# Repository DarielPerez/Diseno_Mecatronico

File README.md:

Este repositorio contiene material relacionado al diseño mecatronico desde documentos hasta diseños de pcb y mucho más abarcando eletronica, diseño 3D, busqueda de informacion, diesño de PCB, diagramas de circuitos, programacion entre otros.

By: Dariel Perez

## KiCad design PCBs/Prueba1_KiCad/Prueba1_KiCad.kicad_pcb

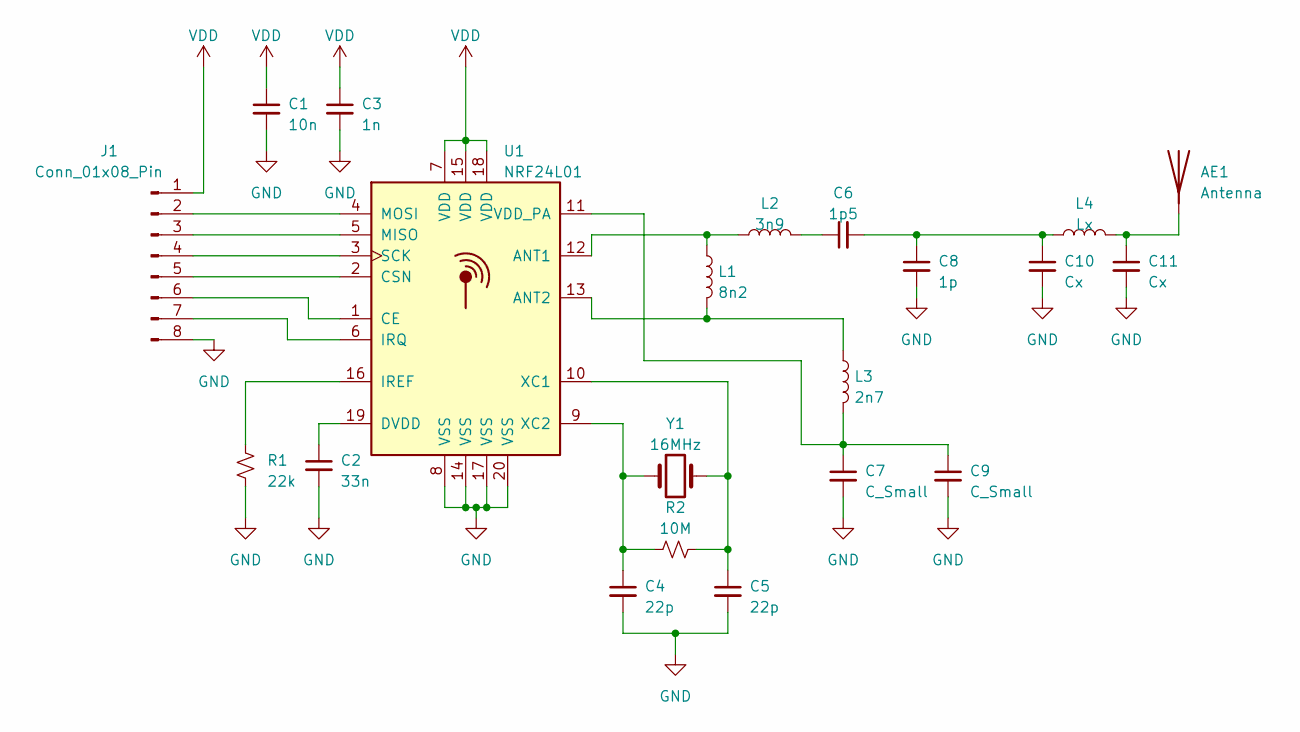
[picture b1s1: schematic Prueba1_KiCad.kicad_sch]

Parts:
AE1: Antenna; Texas_SWRA117D_2.4GHz_Right
C1: 10n; C_0402_1005Metric
C2: 33n; C_0402_1005Metric
C3: 1n; C_0402_1005Metric
C4, C5: 22p; C_0402_1005Metric
C6: 1p5; C_0402_1005Metric
C7, C9: C_Small; C_0402_1005Metric
C8: 1p; C_0402_1005Metric
C10, C11: Cx; C_0402_1005Metric
J1: Conn_01x08_Pin; Hirose_DF13-08P-1.25DSA_1x08_P1.25mm_Vertical
L1: 8n2; L_0402_1005Metric
L2: 3n9; L_0402_1005Metric
L3: 2n7; L_0402_1005Metric
L4: Lx; L_0402_1005Metric
R1: 22k; R_0402_1005Metric_Pad0.72x0.64mm_HandSolder
R2: 10M; R_0402_1005Metric_Pad0.72x0.64mm_HandSolder
U1: NRF24L01; QFN-20-1EP_4x4mm_P0.5mm_EP2.5x2.5mm
Y1: 16MHz; Crystal_SMD_3215-2Pin_3.2x1.5mm

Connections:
GND: C1.2, C2.2, C3.2, C4.2, C5.2, C7.2, C8.2, C9.2, C10.2, C11.2, J1.8, R1.2, U1.8 (VSS), U1.14 (VSS), U1.17 (VSS), U1.20 (VSS)
unnamed: AE1.1 (A), C11.1, L4.2
unnamed: C6.1, L2.2
unnamed: C6.2, C8.1, C10.1, L4.1
unnamed: J1.2, U1.4 (MOSI)
unnamed: J1.3, U1.5 (MISO)
unnamed: J1.4, U1.3 (SCK)
unnamed: J1.5, U1.2 (CSN)
unnamed: J1.6, U1.1 (CE)
unnamed: J1.7, U1.6 (IRQ)
unnamed: L1.1, L2.1, U1.12 (ANT1)
unnamed: L1.2, L3.1, U1.13 (ANT2)
unnamed: C2.1, U1.19 (DVDD)
unnamed: R1.1, U1.16 (IREF)
unnamed: C7.1, C9.1, L3.2, U1.11 (VDD_PA)
unnamed: C5.1, R2.2, U1.10 (XC1), Y1.2
unnamed: C4.1, R2.1, U1.9 (XC2), Y1.1
VDD: C1.1, C3.1, J1.1, U1.7 (VDD), U1.15 (VDD), U1.18 (VDD)

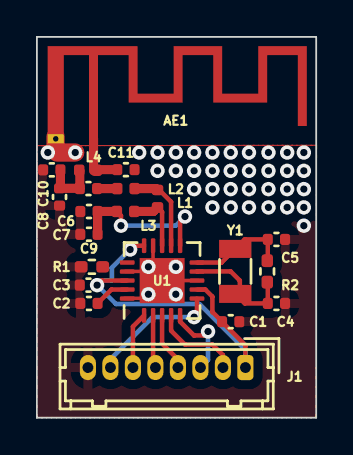
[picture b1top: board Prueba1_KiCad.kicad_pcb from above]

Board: 2 copper layers, 15.5 x 21.2 mm, 21 parts (0 on the bottom side), 18 nets.
